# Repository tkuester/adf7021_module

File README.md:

# ADF7021 Module

Per a discussion with SP5WWP, it would be advantageous to the M17 project to
have a breakout board that can be uesd to prototype with the AD7021 module.
While Analog provides a reasonably priced development module, it is difficult
to modify, and doesn't integrate well into other projects.

Given this, the module should be...

 - Hackable
   - Easy to use as a standalone board (ie: 0.1" headers)
   - Assemble with hobbyist level equipment
   - Financially accessable, limit difficult to source parts
 - Modular
   - Minimize commitments like filter topology / amplifier output
     - Can use as TX, RX, or TX/RX (two SMA conns)
   - Optional footprints to allow for various configurations
 - Designed to integrate into later projects
   - RF shileding footprint
   - Mounting holes, pluggable connectors, etc
 - Not designed for the TR-9
   - Suspect TR-9 needs tighter integration
   - Would be nice, but requirements seem to conflict

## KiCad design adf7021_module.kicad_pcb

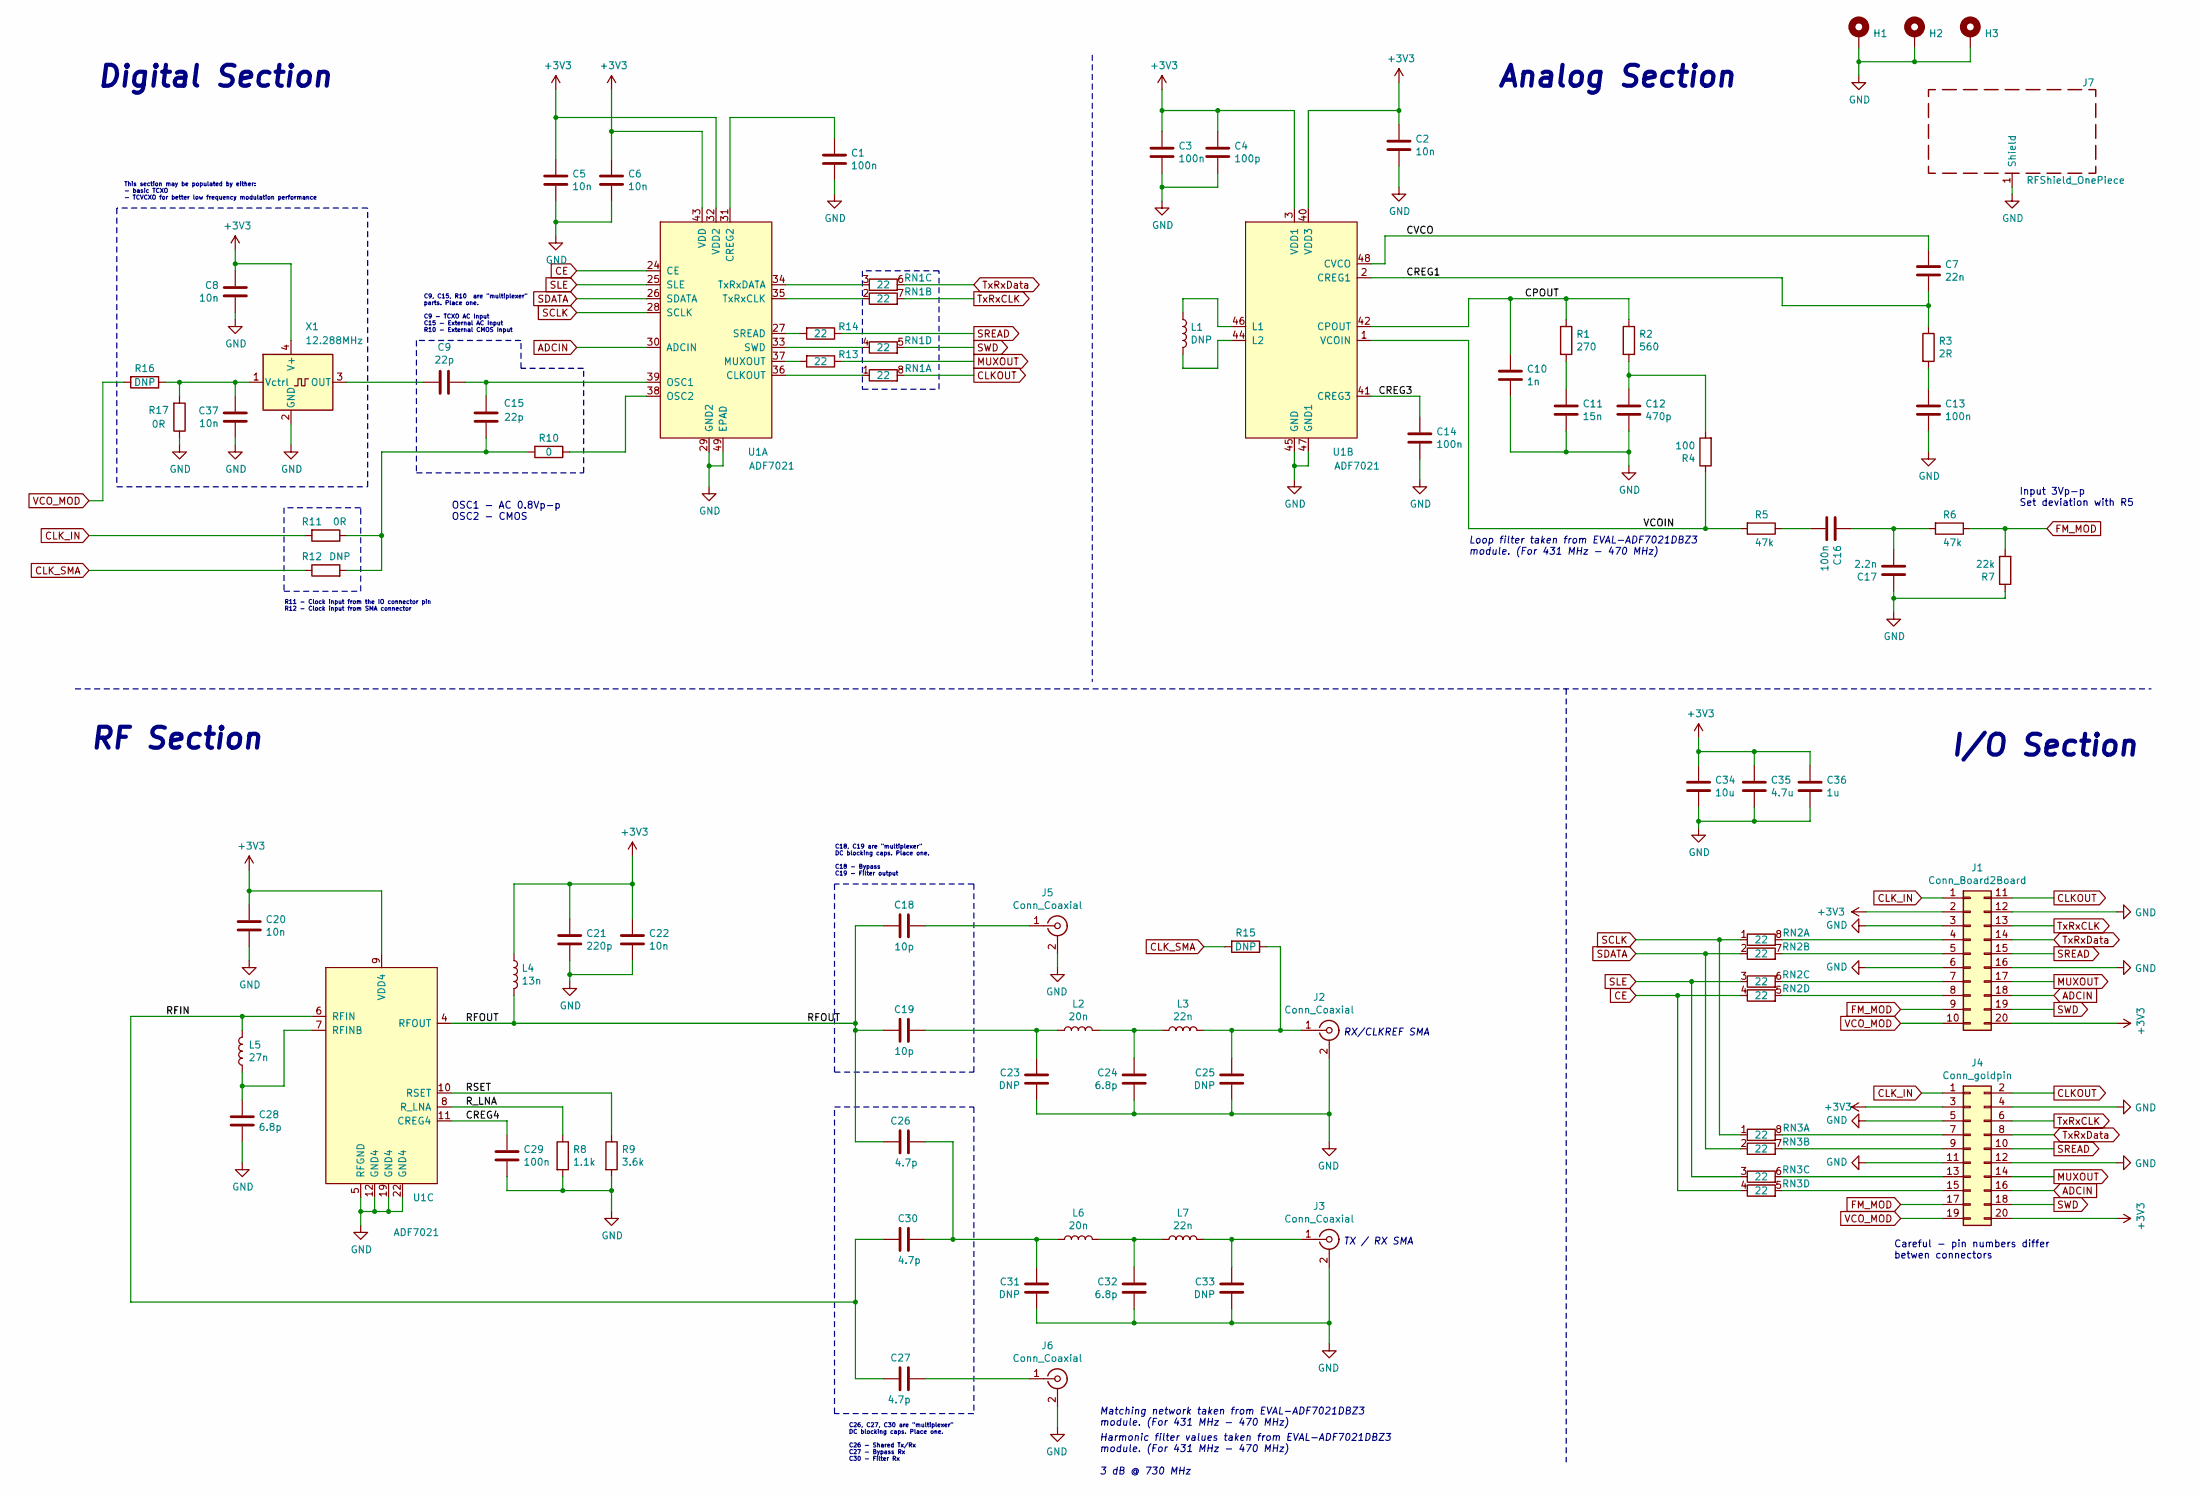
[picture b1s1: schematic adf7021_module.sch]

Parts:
C1, C3, C13, C14, C16, C29: 100n; C_0402_1005Metric_Pad0.74x0.62mm_HandSolder
C2, C5, C6, C8, C20, C22, C37: 10n; C_0402_1005Metric_Pad0.74x0.62mm_HandSolder
C4: 100p; C_0402_1005Metric_Pad0.74x0.62mm_HandSolder
C7: 22n; C_0402_1005Metric_Pad0.74x0.62mm_HandSolder
C9, C15: 22p; C_0402_1005Metric_Pad0.74x0.62mm_HandSolder
C10: 1n; C_0402_1005Metric_Pad0.74x0.62mm_HandSolder
C11: 15n; C_0402_1005Metric_Pad0.74x0.62mm_HandSolder
C12: 470p; C_0402_1005Metric_Pad0.74x0.62mm_HandSolder
C17: 2.2n; C_0402_1005Metric_Pad0.74x0.62mm_HandSolder
C18, C19: 10p; C_0402_1005Metric_Pad0.74x0.62mm_HandSolder
C21: 220p; C_0402_1005Metric_Pad0.74x0.62mm_HandSolder
C23, C25, C31, C33: DNP; C_0402_1005Metric_Pad0.74x0.62mm_HandSolder
C24, C28, C32: 6.8p; C_0402_1005Metric_Pad0.74x0.62mm_HandSolder
C26, C27, C30: 4.7p; C_0402_1005Metric_Pad0.74x0.62mm_HandSolder
C34: 10u; C_0603_1608Metric_Pad1.08x0.95mm_HandSolder
C35: 4.7u; C_0603_1608Metric_Pad1.08x0.95mm_HandSolder
C36: 1u; C_0603_1608Metric_Pad1.08x0.95mm_HandSolder
H1, H2, H3: MountingHole_Pad; MountingHole_2.2mm_M2_Pad_TopBottom
J1: Conn_Board2Board; Hirose_DF12_DF12E3.0-20DP-0.5V_2x10_P0.50mm_Vertical
J2, J3: Conn_Coaxial; SMA_Molex_73251-2200_Horizontal
J4: Conn_goldpin; PinSocket_2x10_P2.54mm_Vertical
J5, J6: Conn_Coaxial; U.FL_Hirose_U.FL-R-SMT-1_Vertical
J7: RFShield_OnePiece; Laird_Technologies_BMI-S-205-F_38.10x25.40mm
L1: DNP; L_0402_1005Metric_Pad0.77x0.64mm_HandSolder
L2, L6: 20n; L_0402_1005Metric_Pad0.77x0.64mm_HandSolder
L3, L7: 22n; L_0402_1005Metric_Pad0.77x0.64mm_HandSolder
L4: 13n; L_0402_1005Metric_Pad0.77x0.64mm_HandSolder
L5: 27n; L_0402_1005Metric_Pad0.77x0.64mm_HandSolder
R1: 270; R_0402_1005Metric_Pad0.72x0.64mm_HandSolder
R2: 560; R_0402_1005Metric_Pad0.72x0.64mm_HandSolder
R3: 2R; R_0402_1005Metric_Pad0.72x0.64mm_HandSolder
R4: 100; R_0402_1005Metric_Pad0.72x0.64mm_HandSolder
R5, R6: 47k; R_0402_1005Metric_Pad0.72x0.64mm_HandSolder
R7: 22k; R_0402_1005Metric_Pad0.72x0.64mm_HandSolder
R8: 1.1k; R_0402_1005Metric_Pad0.72x0.64mm_HandSolder
R9: 3.6k; R_0402_1005Metric_Pad0.72x0.64mm_HandSolder
R10: 0; R_0402_1005Metric_Pad0.72x0.64mm_HandSolder
R11, R17: 0R; R_0402_1005Metric_Pad0.72x0.64mm_HandSolder
R12, R15, R16: DNP; R_0402_1005Metric_Pad0.72x0.64mm_HandSolder
R13, R14: 22; R_0402_1005Metric_Pad0.72x0.64mm_HandSolder
RN1, RN2, RN3: 22; R_Array_Concave_4x0402
U1: ADF7021; QFN-48-1EP_7x7mm_P0.5mm_EP5.3x5.3mm
X1: 12.288MHz; Oscillator_SMD_EuroQuartz_XO32-4Pin_3.2x2.5mm_HandSoldering

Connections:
+3V3: C2.1, C3.1, C4.1, C5.1, C6.1, C8.1, C20.1, C21.1, C22.1, C34.1, C35.1, C36.1, J1.2, J1.20, J4.3, J4.20, L4.1, U1.3 (VDD1), U1.9 (VDD4), U1.32 (VDD2), U1.40 (VDD3), U1.43 (VDD), X1.4 (V+)
/CPOUT: C10.1, R1.1, R2.1, U1.42 (CPOUT)
/CREG1: C7.2, R3.1, U1.2 (CREG1)
/CREG3: C14.1, U1.41 (CREG3)
/CREG4: C29.1, U1.11 (CREG4)
/CVCO: C7.1, U1.48 (CVCO)
/RFIN: C27.1, C30.2, L5.2, U1.6 (RFIN)
/RFOUT: C18.2, C19.2, C26.1, L4.2, U1.4 (RFOUT)
/RSET: R9.1, U1.10 (RSET)
/R_LNA: R8.1, U1.8 (R_LNA)
/VCOIN: R4.1, R5.2, U1.1 (VCOIN)
ADCIN: J1.18, J4.16, U1.30 (ADCIN)
CE: RN2.4 (R4.1), RN3.4 (R4.1), U1.24 (CE)
CLKOUT: J1.11, J4.2, RN1.8 (R1.2)
CLK_IN: J1.1, J4.1, R11.2
CLK_SMA: R12.1, R15.2
FM_MOD: J1.9, J4.17, R6.1, R7.2
GND: C1.2, C2.2, C3.2, C4.2, C5.2, C6.2, C8.2, C10.2, C11.2, C12.2, C13.2, C14.2, C17.1, C20.2, C21.2, C22.2, C23.2, C24.2, C25.2, C28.2, C29.2, C31.2, C32.2, C33.2, C34.2, C35.2, C36.2, C37.2, H1.1, H2.1, H3.1, J1.3, J1.6, J1.12, J1.16, J2.2 (Ext), J3.2 (Ext), J4.4, J4.5, J4.11, J4.12, J5.2 (Ext), J6.2 (Ext), J7.1, R7.1, R8.2, R9.2, R17.1, U1.5 (RFGND), U1.12 (GND4), U1.19 (GND4), U1.22 (GND4), U1.29 (GND2), U1.45 (GND), U1.47 (GND1), U1.49 (EPAD), X1.2 (GND)
MUXOUT: J1.17, J4.14, R13.1
unnamed: C1.1, U1.31 (CREG2)
unnamed: C9.2, X1.3 (OUT)
unnamed: C11.1, R1.2
unnamed: C12.1, R2.2, R4.2
unnamed: C13.1, R3.2
unnamed: C15.1, R10.2, R11.1, R12.2
unnamed: C9.1, C15.2, U1.39 (OSC1)
unnamed: C16.1, C17.2, R6.2
unnamed: C16.2, R5.1
unnamed: C18.1, J5.1 (In)
unnamed: C19.1, C23.1, L2.2
unnamed: C24.1, L2.1, L3.2
unnamed: C25.1, J2.1 (In), L3.1, R15.1
unnamed: C26.2, C30.1, C31.1, L6.2
unnamed: C27.2, J6.1 (In)
unnamed: C28.1, L5.1, U1.7 (RFINB)
unnamed: C32.1, L6.1, L7.2
unnamed: C33.1, J3.1 (In), L7.1
unnamed: C37.1, R16.1, R17.2, X1.1 (Vctrl)
unnamed: J1.4, RN2.8 (R1.2)
unnamed: J1.5, RN2.7 (R2.2)
unnamed: J1.7, RN2.6 (R3.2)
unnamed: J1.8, RN2.5 (R4.2)
unnamed: J4.7, RN3.8 (R1.2)
unnamed: J4.9, RN3.7 (R2.2)
unnamed: J4.13, RN3.6 (R3.2)
unnamed: J4.15, RN3.5 (R4.2)
unnamed: L1.1, U1.46 (L1)
unnamed: L1.2, U1.44 (L2)
unnamed: R10.1, U1.38 (OSC2)
unnamed: R13.2, U1.37 (MUXOUT)
unnamed: R14.2, U1.27 (SREAD)
unnamed: RN1.1 (R1.1), U1.36 (CLKOUT)
unnamed: RN1.2 (R2.1), U1.35 (TxRxCLK)
unnamed: RN1.3 (R3.1), U1.34 (TxRxDATA)
unnamed: RN1.4 (R4.1), U1.33 (SWD)
SCLK: RN2.1 (R1.1), RN3.1 (R1.1), U1.28 (SCLK)
SDATA: RN2.2 (R2.1), RN3.2 (R2.1), U1.26 (SDATA)
SLE: RN2.3 (R3.1), RN3.3 (R3.1), U1.25 (SLE)
SREAD: J1.15, J4.10, R14.1
SWD: J1.19, J4.18, RN1.5 (R4.2)
TxRxCLK: J1.13, J4.6, RN1.7 (R2.2)
TxRxData: J1.14, J4.8, RN1.6 (R3.2)
VCO_MOD: J1.10, J4.19, R16.2

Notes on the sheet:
Digital Section
Analog Section
Loop filter taken from EVAL-ADF7021DBZ3 module. (For 431 MHz - 470 MHz)
Matching network taken from EVAL-ADF7021DBZ3 module. (For 431 MHz - 470 MHz)
OSC1 - AC 0.8Vp-p OSC2 - CMOS
Input 3Vp-p Set deviation with R5
C26, C27, C30 are "multiplexer" DC blocking caps. Place one. C26 - Shared Tx/Rx C27 - Bypass Rx C30 - Filter Rx
C18, C19 are "multiplexer" DC blocking caps. Place one. C18 - Bypass C19 - Filter output
C9, C15, R10 are "multiplexer" parts. Place one. C9 - TCXO AC Input C15 - External AC Input R10 - External CMOS Input
I/O Section
Harmonic filter values taken from EVAL-ADF7021DBZ3 module. (For 431 MHz - 470 MHz) 3 dB @ 730 MHz
TX / RX SMA
RX/CLKREF SMA
Careful - pin numbers differ betwen connectors
RF Section
R11 - Clock input from the IO connector pin R12 - Clock input from SMA connector
This section may be populated by either: - basic TCXO - TCVCXO for better low frequency modulation performance

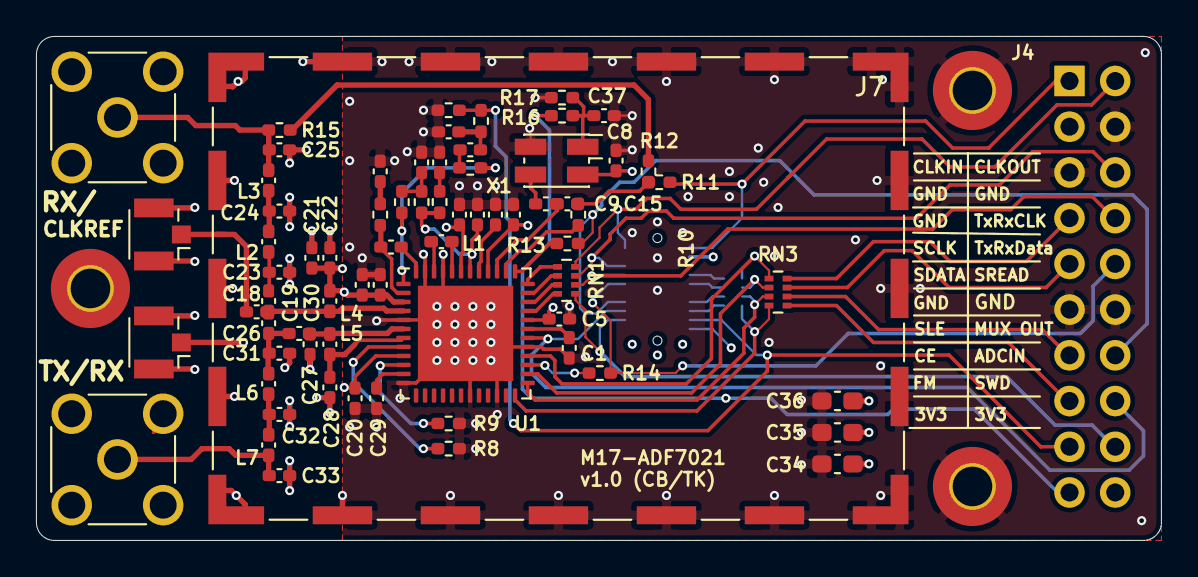
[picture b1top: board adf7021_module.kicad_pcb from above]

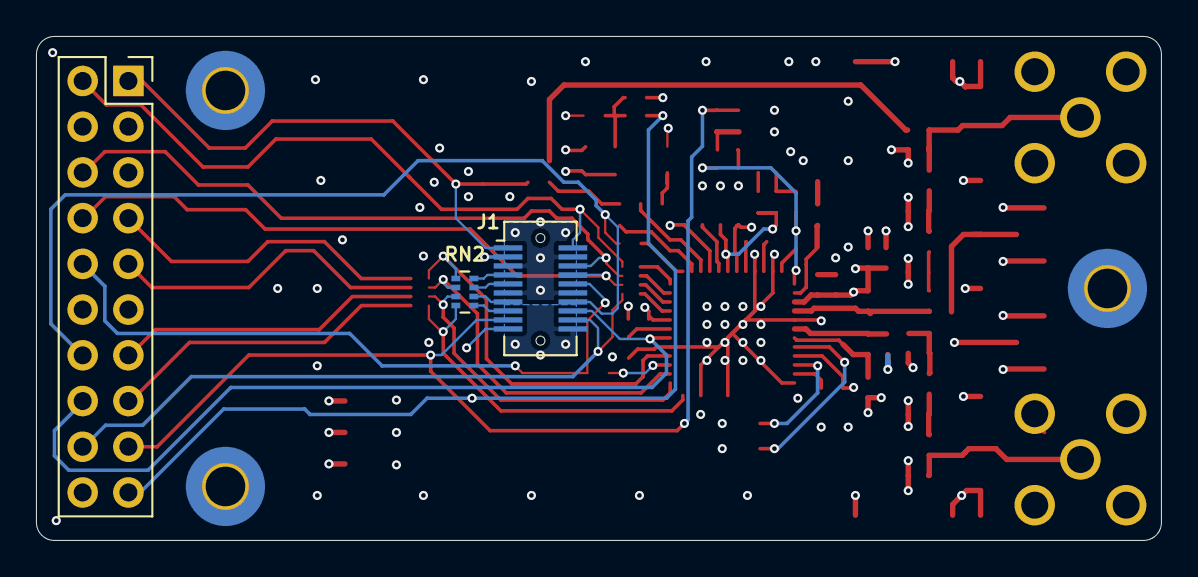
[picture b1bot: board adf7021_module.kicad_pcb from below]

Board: 4 copper layers, 62.5 x 28.0 mm, 76 parts (3 on the bottom side), 63 nets.

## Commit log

2020-11-20 Adding modular ADF7021 library
2020-11-20 Initial commit of schematic
2020-11-24 Adding documentation
2020-11-24 Clarifying a few points
2020-12-05 Adding reference documents
2020-12-05 Add external clock input SMA
2020-12-05 RF output chain, labels for digital pins
2020-12-05 Improving documentation on schematic
2020-12-05 Adding 2x10 data headers, unifying CLK_IN signal
2020-12-05 Annotating parts
2020-12-05 Adding series resistors on clock / data pins
2020-12-05 Tidying up organization of FM Mod section
2020-12-05 Adding mounting holes
2020-12-05 Adding bus resistors on all inputs / outputs
    You get a bus resistor! You get a bus resistor!
    EVERYONE GETS A BUS RESISTOOOOORRR!!1
2020-12-07 rough component placement, stackup definition
2020-12-09 some component placement attempts
2020-12-13 some more layout attempts
2020-12-13 Rounding corners of PCB
2020-12-13 Adding mechanical dimensions, adjusting location of J1
2020-12-13 Giving SMA's more generous spacing from edge
2020-12-13 Adding 3V3/GND planes to internal layers
2020-12-13 Shrinking vias to OSH Park spec (10 mil drill, 20 mil dia)
    This is larger than JLCPCB's spec. Additionally, while OSH Park can
    technically handle 18 mil dia, that results in 4 mil annular rings,
    which may push the PCB tech a little too far. (Minimum trace/space is
    5 mil.)
2020-12-13 Fixing pin that was off-grid
2020-12-13 Routing WIP
    * Trying for symmetrical filter layout
    * Moving non-essential circuitry (ie: FM_MOD filter) away from U1
    * GND pad for J1 on bottom
    * Trying to have SMD orientation match schematic (ie: L5/C28)
2020-12-13 RF bypass will use auxillary U.FL instead of SMA
    This greatly reduces schematic complexity. Since this is more of a
    "debug" feature that we do not anticipate using much, it seems ok to
    make this a secondary connector.
2020-12-13 Swapping ADCIN and SWD for routing sanity
2020-12-13 Most traces routed, except debug U.FL's
    * Care to prevent plane slots on In1/In2 w/ vias
2020-12-13 Adding pinout silkscreen
2020-12-13 Moving mounting holes to make room for U.FL's
    * 0 unrouted traces
    * DRC clear
2020-12-13 Hiding silk screen that won't fit
2020-12-13 Preliminary via stitching
2020-12-13 Version silkscreen, via stitching under U1
2021-01-02 adding shield, moving uFL debug connectors, adding optional SMA clock source input
2021-01-02 adding PDF schematic
2021-01-02 adding application note
2021-01-10 adding VFO pin
2021-01-27 adding fab outputs
